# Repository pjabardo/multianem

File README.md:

# multianem - Multiple channel thermistor based CTA anemometer

This projecto has as its objective implement low cost multiple channel thermistor based constant temperature anemometer systems. This projecto includes the KICAD projects for the sensors and data acquisition system.

The main objective is to design a robust, cheap and easily sourced system. By easily sourced system, I mean that the components should be readily available in Brazil.

The project has different parts:

 * `multiname`: Basic board with 8 sensors.
 * `esp32-daq-board`: Data acquisition system for 32 channels
 * `multianem-box`: 3D printed/CNC casing for the system.
 * `multianemdaq`: embedded data acquisition software for the ESP32
 * Other software: data acquisition for Julia, R and Python (nothing to see yet...)

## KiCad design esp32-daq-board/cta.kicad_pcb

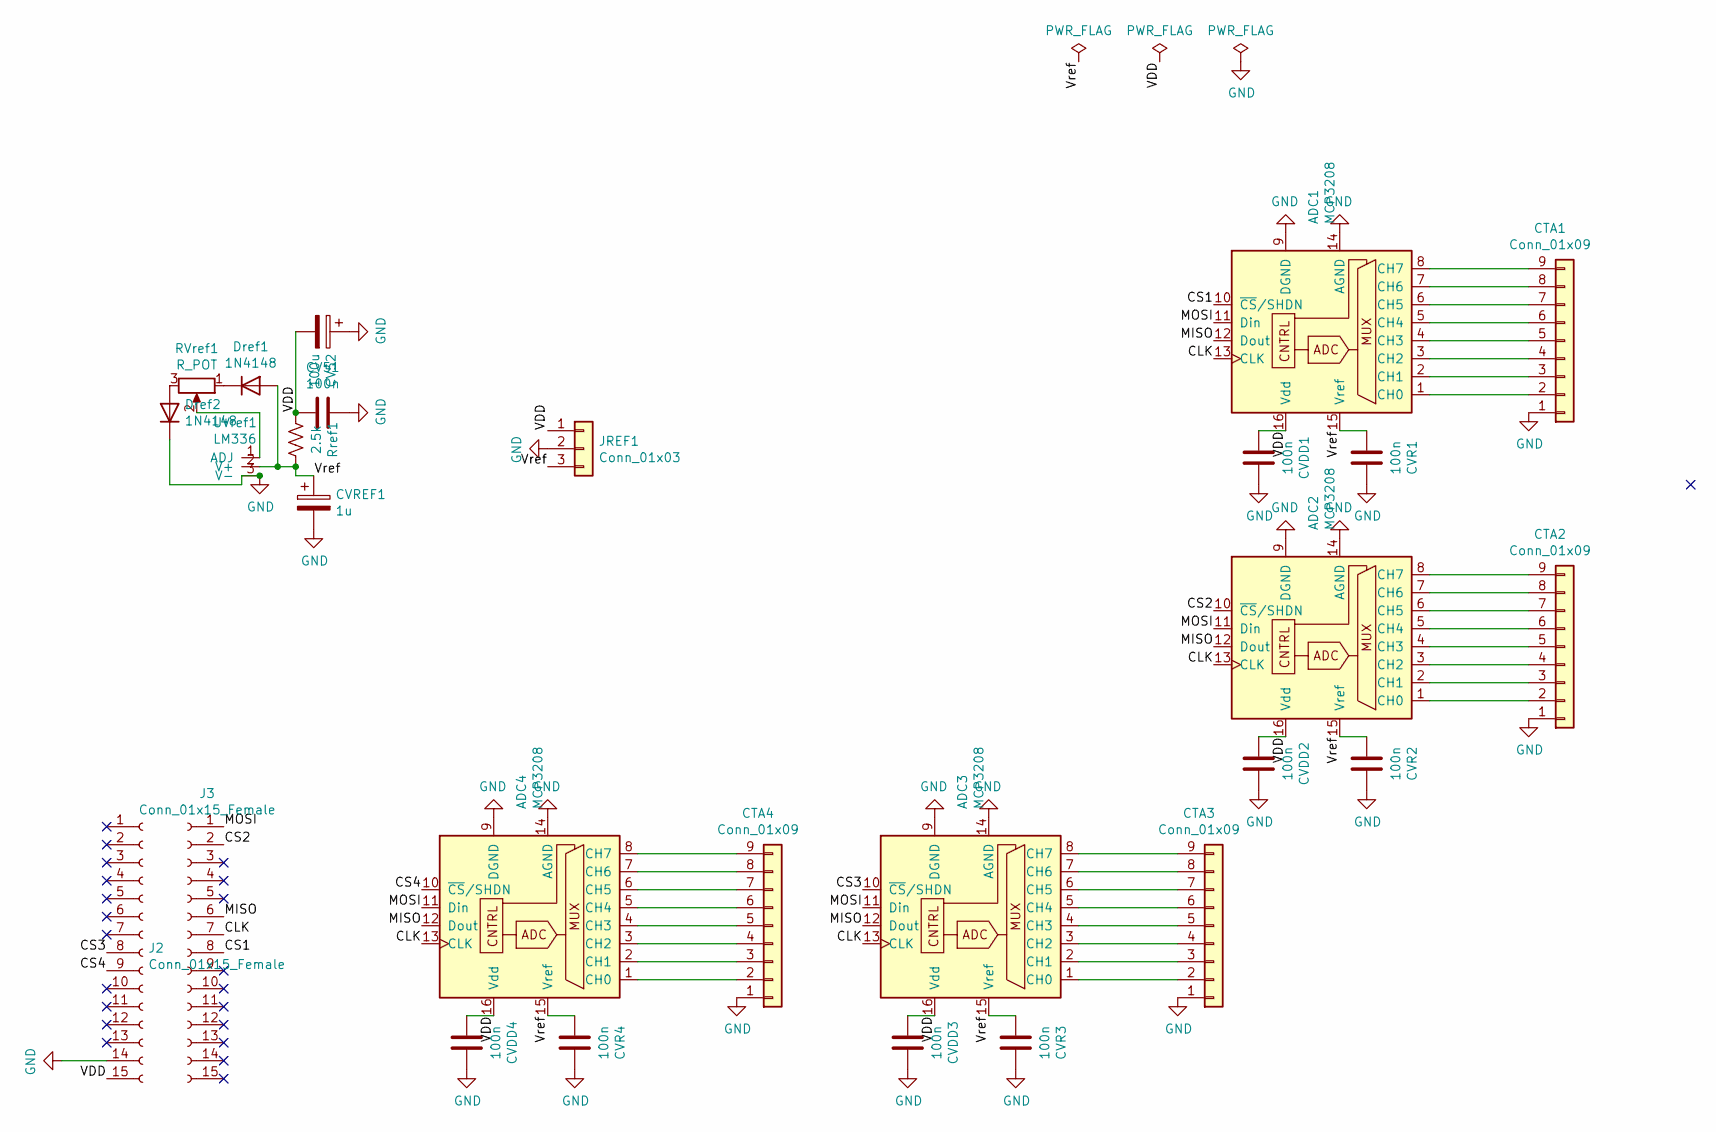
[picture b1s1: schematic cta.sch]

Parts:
ADC1, ADC2, ADC3, ADC4: MCP3208; DIP-16_W7.62mm_LongPads
CTA1, CTA2, CTA3, CTA4: Conn_01x09; PinHeader_1x09_P2.54mm_Vertical
CV51: 100n; C_Rect_L7.2mm_W3.0mm_P5.00mm_FKS2_FKP2_MKS2_MKP2
CV52: 100u; CP_Radial_D6.3mm_P2.50mm
CVDD1, CVDD2, CVDD3, CVDD4: 100n; C_Rect_L7.2mm_W3.0mm_P5.00mm_FKS2_FKP2_MKS2_MKP2
CVR1, CVR2, CVR3, CVR4: 100n; C_Rect_L7.2mm_W3.0mm_P5.00mm_FKS2_FKP2_MKS2_MKP2
CVREF1: 1u; CP_Radial_D4.0mm_P2.00mm
Dref1, Dref2: 1N4148; D_DO-35_SOD27_P7.62mm_Horizontal
J2, J3: Conn_01x15_Female; PinSocket_1x15_P2.54mm_Vertical
JREF1: Conn_01x03; TerminalBlock_bornier-3_P5.08mm
RVref1: R_POT; Potentiometer_Bourns_3296W_Vertical
Rref1: 2.5k; R_Axial_DIN0207_L6.3mm_D2.5mm_P10.16mm_Horizontal
UVref1: LM336; TO-92L_Inline_Wide

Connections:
/CLK: ADC1.13 (CLK), ADC2.13 (CLK), ADC3.13 (CLK), ADC4.13 (CLK), J3.7
/CS1: ADC1.10 (~CS~/SHDN), J3.8
/CS2: ADC2.10 (~CS~/SHDN), J3.2
/CS3: ADC3.10 (~CS~/SHDN), J2.8
/CS4: ADC4.10 (~CS~/SHDN), J2.9
/MISO: ADC1.12 (Dout), ADC2.12 (Dout), ADC3.12 (Dout), ADC4.12 (Dout), J3.6
/MOSI: ADC1.11 (Din), ADC2.11 (Din), ADC3.11 (Din), ADC4.11 (Din), J3.1
/VDD: ADC1.16 (Vdd), ADC2.16 (Vdd), ADC3.16 (Vdd), ADC4.16 (Vdd), CV51.2, CV52.2, CVDD1.2, CVDD2.2, CVDD3.2, CVDD4.2, J2.15, JREF1.1, Rref1.2
/Vref: ADC1.15 (Vref), ADC2.15 (Vref), ADC3.15 (Vref), ADC4.15 (Vref), CVR1.2, CVR2.2, CVR3.2, CVR4.2, CVREF1.1, Dref1.2 (A), JREF1.3, Rref1.1, UVref1.2 (V+)
GND: ADC1.9 (DGND), ADC1.14 (AGND), ADC2.9 (DGND), ADC2.14 (AGND), ADC3.9 (DGND), ADC3.14 (AGND), ADC4.9 (DGND), ADC4.14 (AGND), CTA1.1, CTA2.1, CTA3.1, CTA4.1, CV51.1, CV52.1, CVDD1.1, CVDD2.1, CVDD3.1, CVDD4.1, CVR1.1, CVR2.1, CVR3.1, CVR4.1, CVREF1.2, Dref2.1 (K), J2.14, JREF1.2, UVref1.3 (V-)
unnamed: ADC1.1 (CH0), CTA1.2
unnamed: ADC1.2 (CH1), CTA1.3
unnamed: ADC1.3 (CH2), CTA1.4
unnamed: ADC1.4 (CH3), CTA1.5
unnamed: ADC1.5 (CH4), CTA1.6
unnamed: ADC1.6 (CH5), CTA1.7
unnamed: ADC1.7 (CH6), CTA1.8
unnamed: ADC1.8 (CH7), CTA1.9
unnamed: ADC2.1 (CH0), CTA2.2
unnamed: ADC2.2 (CH1), CTA2.3
unnamed: ADC2.3 (CH2), CTA2.4
unnamed: ADC2.4 (CH3), CTA2.5
unnamed: ADC2.5 (CH4), CTA2.6
unnamed: ADC2.6 (CH5), CTA2.7
unnamed: ADC2.7 (CH6), CTA2.8
unnamed: ADC2.8 (CH7), CTA2.9
unnamed: ADC3.1 (CH0), CTA3.2
unnamed: ADC3.2 (CH1), CTA3.3
unnamed: ADC3.3 (CH2), CTA3.4
unnamed: ADC3.4 (CH3), CTA3.5
unnamed: ADC3.5 (CH4), CTA3.6
unnamed: ADC3.6 (CH5), CTA3.7
unnamed: ADC3.7 (CH6), CTA3.8
unnamed: ADC3.8 (CH7), CTA3.9
unnamed: ADC4.1 (CH0), CTA4.2
unnamed: ADC4.2 (CH1), CTA4.3
unnamed: ADC4.3 (CH2), CTA4.4
unnamed: ADC4.4 (CH3), CTA4.5
unnamed: ADC4.5 (CH4), CTA4.6
unnamed: ADC4.6 (CH5), CTA4.7
unnamed: ADC4.7 (CH6), CTA4.8
unnamed: ADC4.8 (CH7), CTA4.9
unnamed: Dref1.1 (K), RVref1.1
unnamed: Dref2.2 (A), RVref1.3
unnamed: RVref1.2, UVref1.1 (ADJ)

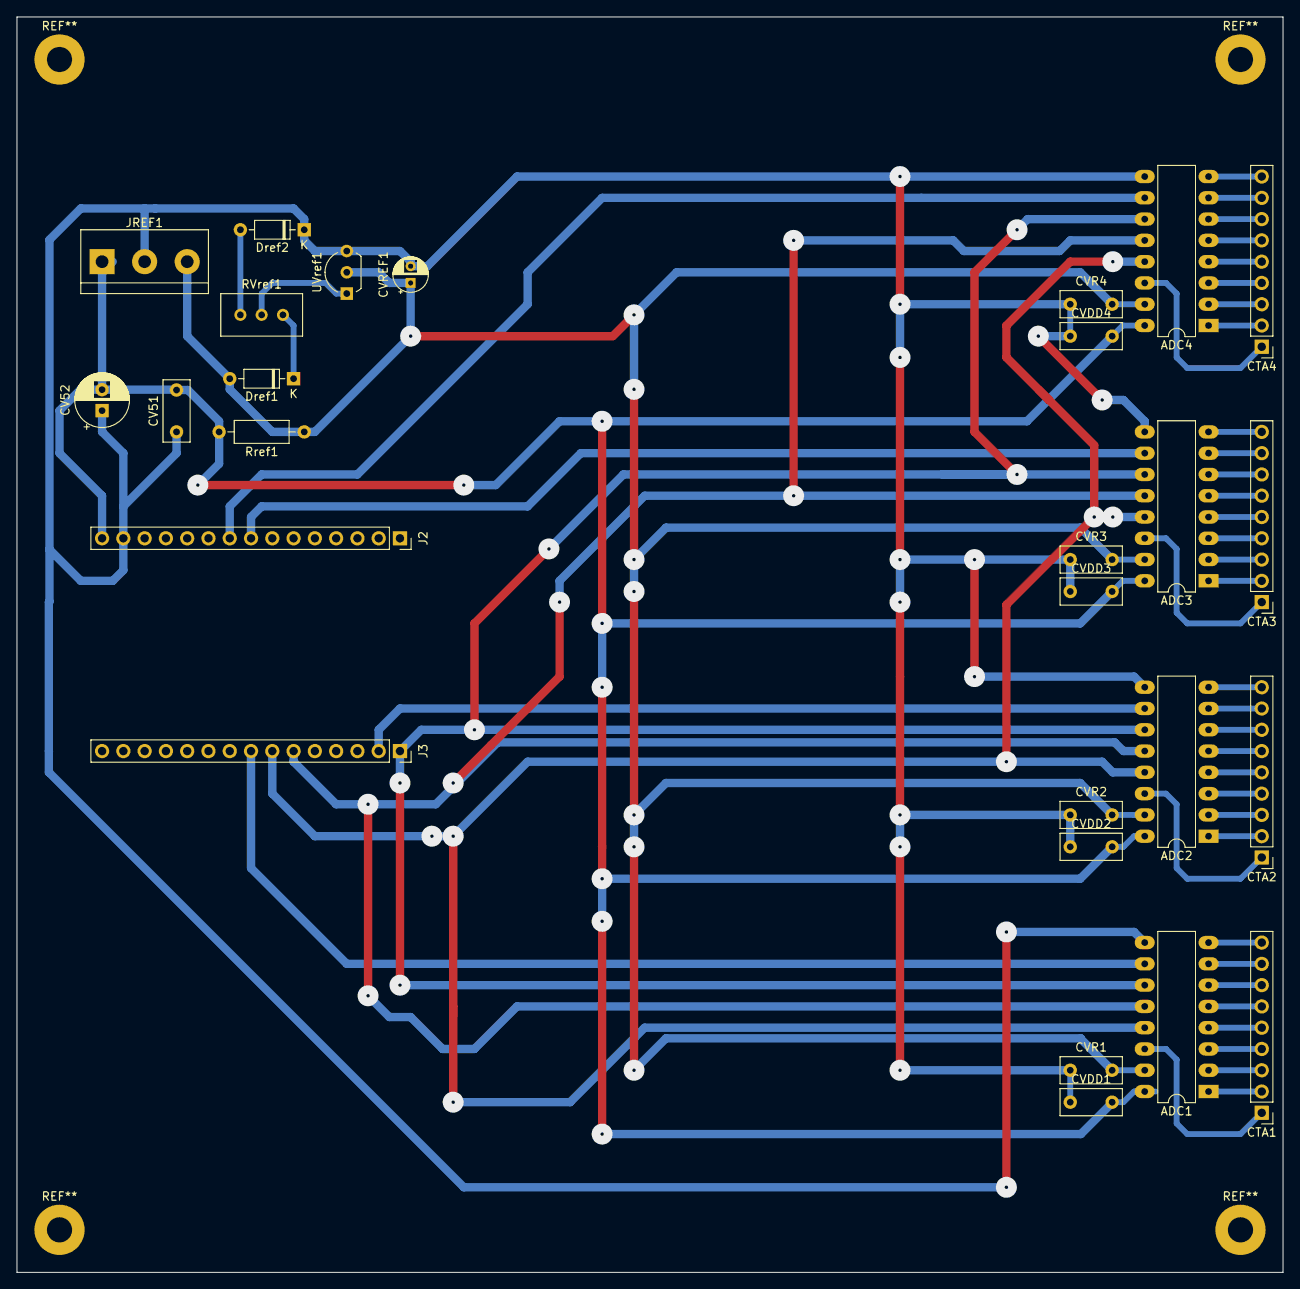
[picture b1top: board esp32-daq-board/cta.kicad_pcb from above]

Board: 2 copper layers, 151.1 x 149.9 mm, 27 parts (0 on the bottom side), 45 nets.

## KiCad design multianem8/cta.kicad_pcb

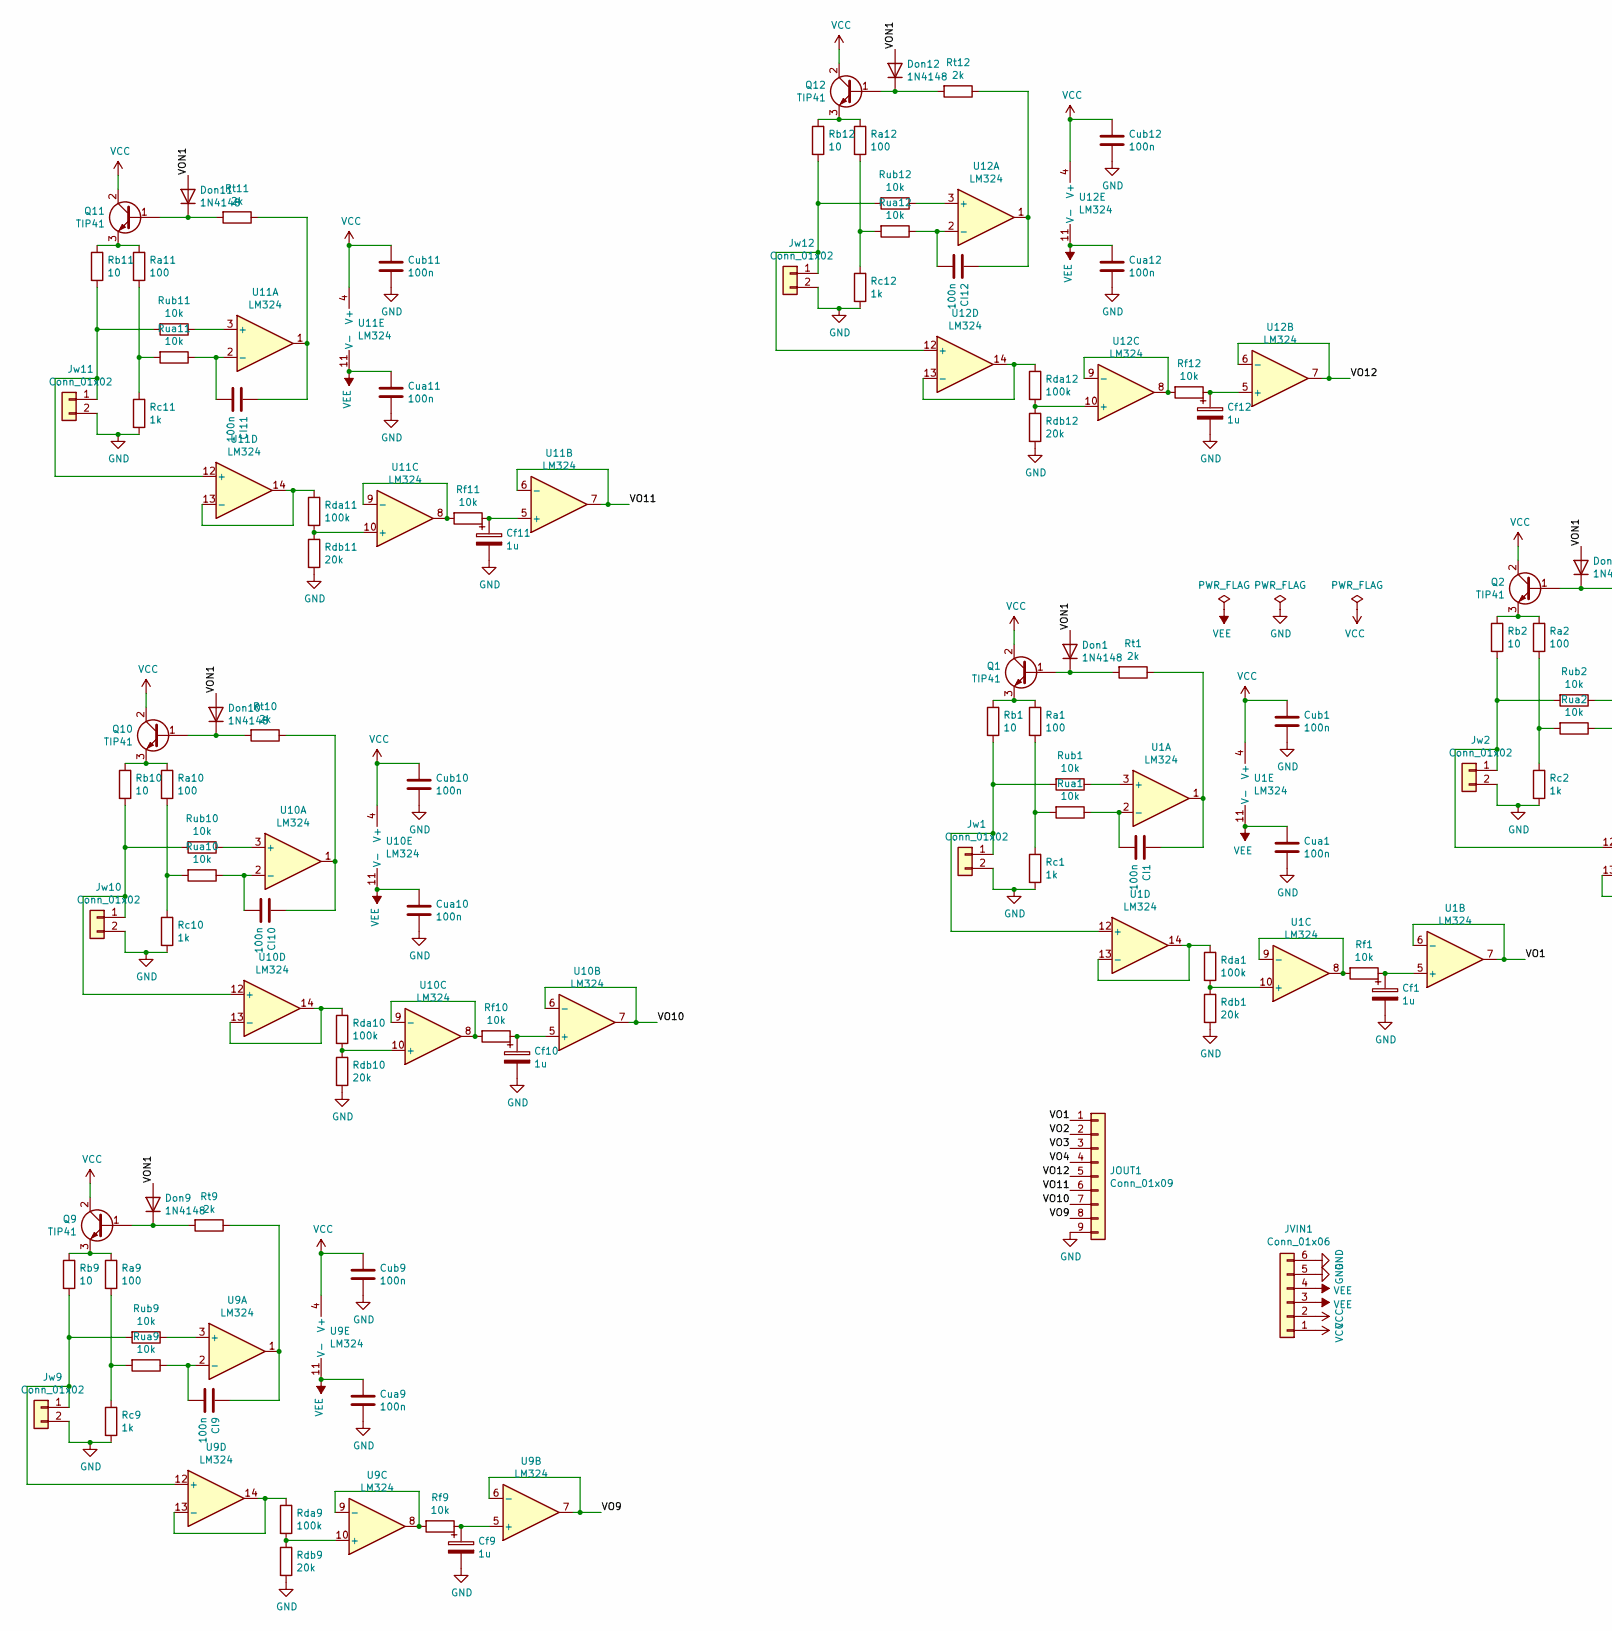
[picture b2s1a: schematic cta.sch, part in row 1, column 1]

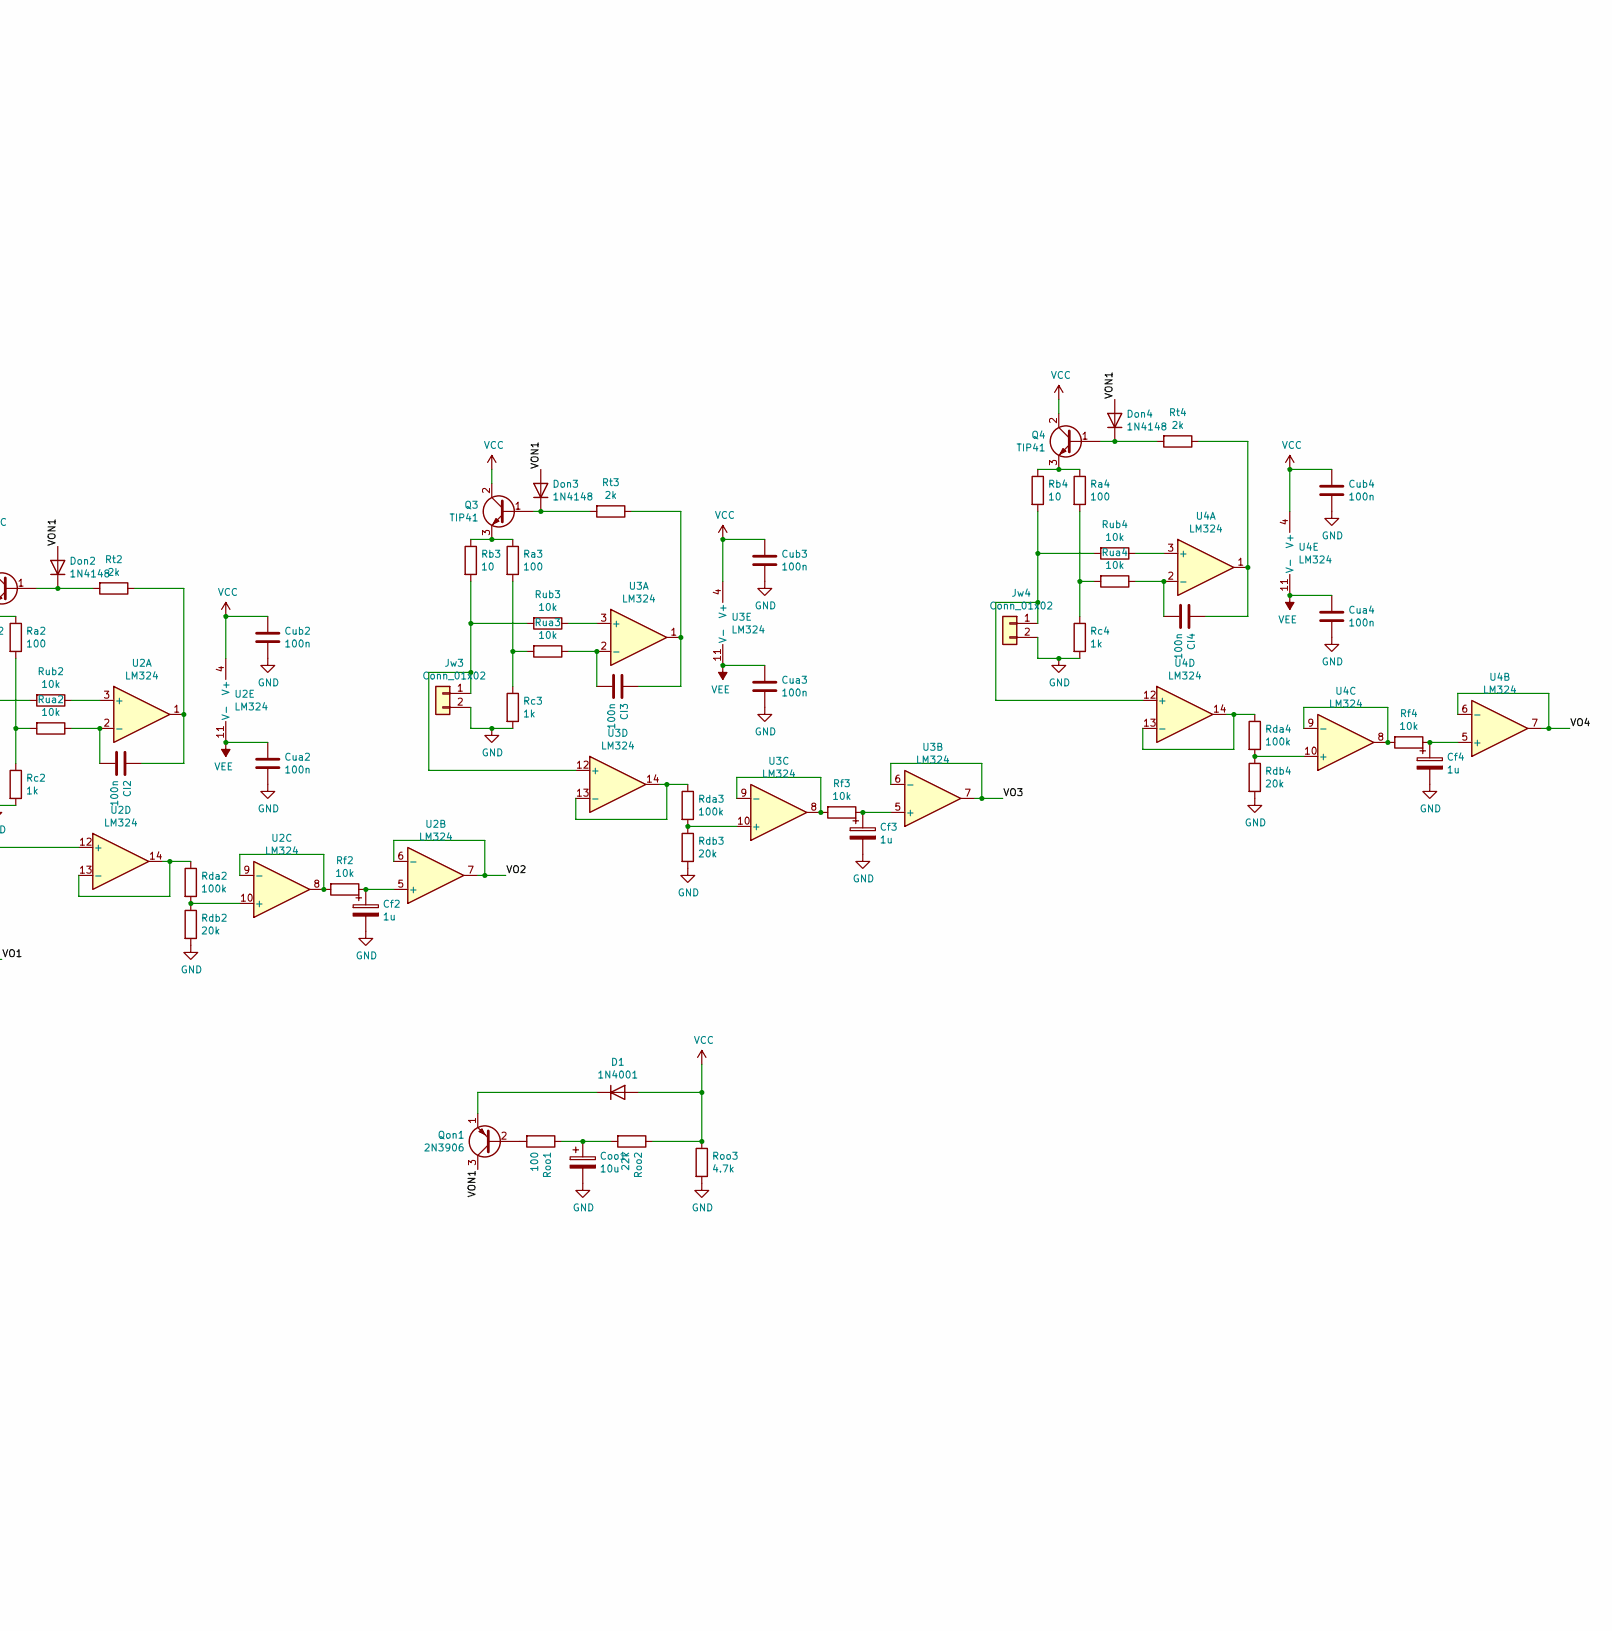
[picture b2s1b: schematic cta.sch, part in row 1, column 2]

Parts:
CI1, CI2, CI3, CI4, CI9, CI10, CI11, CI12: 100n; C_Rect_L7.2mm_W3.5mm_P5.00mm_FKS2_FKP2_MKS2_MKP2
Cf1, Cf2, Cf3, Cf4, Cf9, Cf10, Cf11, Cf12: 1u; CP_Radial_D5.0mm_P2.50mm
Coo1: 10u; CP_Radial_D5.0mm_P2.50mm
Cua1, Cua2, Cua3, Cua4, Cua9, Cua10, Cua11, Cua12: 100n; C_Disc_D5.0mm_W2.5mm_P2.50mm
Cub1, Cub2, Cub3, Cub4, Cub9, Cub10, Cub11, Cub12: 100n; C_Disc_D5.0mm_W2.5mm_P2.50mm
D1: 1N4001; D_DO-41_SOD81_P10.16mm_Horizontal
Don1, Don2, Don3, Don4, Don9, Don10, Don11, Don12: 1N4148; D_DO-35_SOD27_P7.62mm_Horizontal
JOUT1: Conn_01x09; PinHeader_1x09_P2.54mm_Vertical
JVIN1: Conn_01x06; TerminalBlock_bornier-6_P5.08mm
Jw1, Jw2, Jw3, Jw4, Jw9, Jw10, Jw11, Jw12: Conn_01x02; PinHeader_1x02_P2.54mm_Vertical
Q1, Q2, Q3, Q4, Q9, Q10, Q11, Q12: TIP41; TO-220-3_Vertical
Qon1: 2N3906; TO-92_Inline_Wide
Ra1, Ra2, Ra3, Ra4, Ra9, Ra10, Ra11, Ra12: 100; R_Axial_DIN0207_L6.3mm_D2.5mm_P10.16mm_Horizontal
Rb1, Rb2, Rb3, Rb4, Rb9, Rb10, Rb11, Rb12: 10; R_Axial_DIN0414_L11.9mm_D4.5mm_P15.24mm_Horizontal
Rc1, Rc2, Rc3, Rc4, Rc9, Rc10, Rc11, Rc12: 1k; R_Axial_DIN0207_L6.3mm_D2.5mm_P10.16mm_Horizontal
Rda1, Rda2, Rda3, Rda4, Rda9, Rda10, Rda11, Rda12: 100k; R_Axial_DIN0207_L6.3mm_D2.5mm_P10.16mm_Horizontal
Rdb1, Rdb2, Rdb3, Rdb4, Rdb9, Rdb10, Rdb11, Rdb12: 20k; R_Axial_DIN0207_L6.3mm_D2.5mm_P10.16mm_Horizontal
Rf1, Rf2, Rf3, Rf4, Rf9, Rf10, Rf11, Rf12: 10k; R_Axial_DIN0207_L6.3mm_D2.5mm_P10.16mm_Horizontal
Roo1: 100; R_Axial_DIN0207_L6.3mm_D2.5mm_P10.16mm_Horizontal
Roo2: 22k; R_Axial_DIN0207_L6.3mm_D2.5mm_P10.16mm_Horizontal
Roo3: 4.7k; R_Axial_DIN0207_L6.3mm_D2.5mm_P10.16mm_Horizontal
Rt1, Rt2, Rt3, Rt4, Rt9, Rt10, Rt11, Rt12: 2k; R_Axial_DIN0207_L6.3mm_D2.5mm_P10.16mm_Horizontal
Rua1, Rua2, Rua3, Rua4, Rua9, Rua10, Rua11, Rua12: 10k; R_Axial_DIN0207_L6.3mm_D2.5mm_P10.16mm_Horizontal
Rub1, Rub2, Rub3, Rub4, Rub9, Rub10, Rub11, Rub12: 10k; R_Axial_DIN0207_L6.3mm_D2.5mm_P10.16mm_Horizontal
U1, U2, U3, U4, U9, U10, U11, U12: LM324; DIP-14_W7.62mm_LongPads

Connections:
/VO1: JOUT1.1, U1.6 (-), U1.7
/VO2: JOUT1.2, U2.6 (-), U2.7
/VO3: JOUT1.3, U3.6 (-), U3.7
/VO4: JOUT1.4, U4.6 (-), U4.7
/VO9: JOUT1.8, U9.6 (-), U9.7
/VO10: JOUT1.7, U10.6 (-), U10.7
/VO11: JOUT1.6, U11.6 (-), U11.7
/VO12: JOUT1.5, U12.6 (-), U12.7
/VON1: Don1.2 (A), Don2.2 (A), Don3.2 (A), Don4.2 (A), Don9.2 (A), Don10.2 (A), Don11.2 (A), Don12.2 (A), Qon1.3 (C)
GND: Cf1.2, Cf2.2, Cf3.2, Cf4.2, Cf9.2, Cf10.2, Cf11.2, Cf12.2, Coo1.2, Cua1.2, Cua2.2, Cua3.2, Cua4.2, Cua9.2, Cua10.2, Cua11.2, Cua12.2, Cub1.2, Cub2.2, Cub3.2, Cub4.2, Cub9.2, Cub10.2, Cub11.2, Cub12.2, JOUT1.9, JVIN1.5, JVIN1.6, Jw1.2, Jw2.2, Jw3.2, Jw4.2, Jw9.2, Jw10.2, Jw11.2, Jw12.2, Rc1.2, Rc2.2, Rc3.2, Rc4.2, Rc9.2, Rc10.2, Rc11.2, Rc12.2, Rdb1.2, Rdb2.2, Rdb3.2, Rdb4.2, Rdb9.2, Rdb10.2, Rdb11.2, Rdb12.2, Roo3.2
unnamed: CI1.1, Rt1.1, U1.1
unnamed: CI1.2, Rua1.1, U1.2 (-)
unnamed: CI2.1, Rt2.1, U2.1
unnamed: CI2.2, Rua2.1, U2.2 (-)
unnamed: CI3.1, Rt3.1, U3.1
unnamed: CI3.2, Rua3.1, U3.2 (-)
unnamed: CI4.1, Rt4.1, U4.1
unnamed: CI4.2, Rua4.1, U4.2 (-)
unnamed: CI9.1, Rt9.1, U9.1
unnamed: CI9.2, Rua9.1, U9.2 (-)
unnamed: CI10.1, Rt10.1, U10.1
unnamed: CI10.2, Rua10.1, U10.2 (-)
unnamed: CI11.1, Rt11.1, U11.1
unnamed: CI11.2, Rua11.1, U11.2 (-)
unnamed: CI12.1, Rt12.1, U12.1
unnamed: CI12.2, Rua12.1, U12.2 (-)
unnamed: Cf1.1, Rf1.1, U1.5 (+)
unnamed: Cf2.1, Rf2.1, U2.5 (+)
unnamed: Cf3.1, Rf3.1, U3.5 (+)
unnamed: Cf4.1, Rf4.1, U4.5 (+)
unnamed: Cf9.1, Rf9.1, U9.5 (+)
unnamed: Cf10.1, Rf10.1, U10.5 (+)
unnamed: Cf11.1, Rf11.1, U11.5 (+)
unnamed: Cf12.1, Rf12.1, U12.5 (+)
unnamed: Coo1.1, Roo1.1, Roo2.2
unnamed: D1.1 (K), Qon1.1 (E)
unnamed: Don1.1 (K), Q1.1 (B), Rt1.2
unnamed: Don2.1 (K), Q2.1 (B), Rt2.2
unnamed: Don3.1 (K), Q3.1 (B), Rt3.2
unnamed: Don4.1 (K), Q4.1 (B), Rt4.2
unnamed: Don9.1 (K), Q9.1 (B), Rt9.2
unnamed: Don10.1 (K), Q10.1 (B), Rt10.2
unnamed: Don11.1 (K), Q11.1 (B), Rt11.2
unnamed: Don12.1 (K), Q12.1 (B), Rt12.2
unnamed: Jw1.1, Rb1.2, Rub1.2, U1.12 (+)
unnamed: Jw2.1, Rb2.2, Rub2.2, U2.12 (+)
unnamed: Jw3.1, Rb3.2, Rub3.2, U3.12 (+)
unnamed: Jw4.1, Rb4.2, Rub4.2, U4.12 (+)
unnamed: Jw9.1, Rb9.2, Rub9.2, U9.12 (+)
unnamed: Jw10.1, Rb10.2, Rub10.2, U10.12 (+)
unnamed: Jw11.1, Rb11.2, Rub11.2, U11.12 (+)
unnamed: Jw12.1, Rb12.2, Rub12.2, U12.12 (+)
unnamed: Q1.3 (E), Ra1.1, Rb1.1
unnamed: Q2.3 (E), Ra2.1, Rb2.1
unnamed: Q3.3 (E), Ra3.1, Rb3.1
unnamed: Q4.3 (E), Ra4.1, Rb4.1
unnamed: Q9.3 (E), Ra9.1, Rb9.1
unnamed: Q10.3 (E), Ra10.1, Rb10.1
unnamed: Q11.3 (E), Ra11.1, Rb11.1
unnamed: Q12.3 (E), Ra12.1, Rb12.1
unnamed: Qon1.2 (B), Roo1.2
unnamed: Ra1.2, Rc1.1, Rua1.2
unnamed: Ra2.2, Rc2.1, Rua2.2
unnamed: Ra3.2, Rc3.1, Rua3.2
unnamed: Ra4.2, Rc4.1, Rua4.2
unnamed: Ra9.2, Rc9.1, Rua9.2
unnamed: Ra10.2, Rc10.1, Rua10.2
unnamed: Ra11.2, Rc11.1, Rua11.2
unnamed: Ra12.2, Rc12.1, Rua12.2
unnamed: Rda1.1, U1.13 (-), U1.14
unnamed: Rda1.2, Rdb1.1, U1.10 (+)
unnamed: Rda2.1, U2.13 (-), U2.14
unnamed: Rda2.2, Rdb2.1, U2.10 (+)
unnamed: Rda3.1, U3.13 (-), U3.14
unnamed: Rda3.2, Rdb3.1, U3.10 (+)
unnamed: Rda4.1, U4.13 (-), U4.14
unnamed: Rda4.2, Rdb4.1, U4.10 (+)
unnamed: Rda9.1, U9.13 (-), U9.14
unnamed: Rda9.2, Rdb9.1, U9.10 (+)
unnamed: Rda10.1, U10.13 (-), U10.14
unnamed: Rda10.2, Rdb10.1, U10.10 (+)
unnamed: Rda11.1, U11.13 (-), U11.14
unnamed: Rda11.2, Rdb11.1, U11.10 (+)
unnamed: Rda12.1, U12.13 (-), U12.14
unnamed: Rda12.2, Rdb12.1, U12.10 (+)
unnamed: Rf1.2, U1.8, U1.9 (-)
unnamed: Rf2.2, U2.8, U2.9 (-)
unnamed: Rf3.2, U3.8, U3.9 (-)
unnamed: Rf4.2, U4.8, U4.9 (-)
unnamed: Rf9.2, U9.8, U9.9 (-)
unnamed: Rf10.2, U10.8, U10.9 (-)
unnamed: Rf11.2, U11.8, U11.9 (-)
unnamed: Rf12.2, U12.8, U12.9 (-)
unnamed: Rub1.1, U1.3 (+)
unnamed: Rub2.1, U2.3 (+)
unnamed: Rub3.1, U3.3 (+)
unnamed: Rub4.1, U4.3 (+)
unnamed: Rub9.1, U9.3 (+)
unnamed: Rub10.1, U10.3 (+)
unnamed: Rub11.1, U11.3 (+)
unnamed: Rub12.1, U12.3 (+)
VCC: Cub1.1, Cub2.1, Cub3.1, Cub4.1, Cub9.1, Cub10.1, Cub11.1, Cub12.1, D1.2 (A), JVIN1.1, JVIN1.2, Q1.2 (C), Q2.2 (C), Q3.2 (C), Q4.2 (C), Q9.2 (C), Q10.2 (C), Q11.2 (C), Q12.2 (C), Roo2.1, Roo3.1, U1.4 (V+), U2.4 (V+), U3.4 (V+), U4.4 (V+), U9.4 (V+), U10.4 (V+), U11.4 (V+), U12.4 (V+)
VEE: Cua1.1, Cua2.1, Cua3.1, Cua4.1, Cua9.1, Cua10.1, Cua11.1, Cua12.1, JVIN1.3, JVIN1.4, U1.11 (V-), U2.11 (V-), U3.11 (V-), U4.11 (V-), U9.11 (V-), U10.11 (V-), U11.11 (V-), U12.11 (V-)

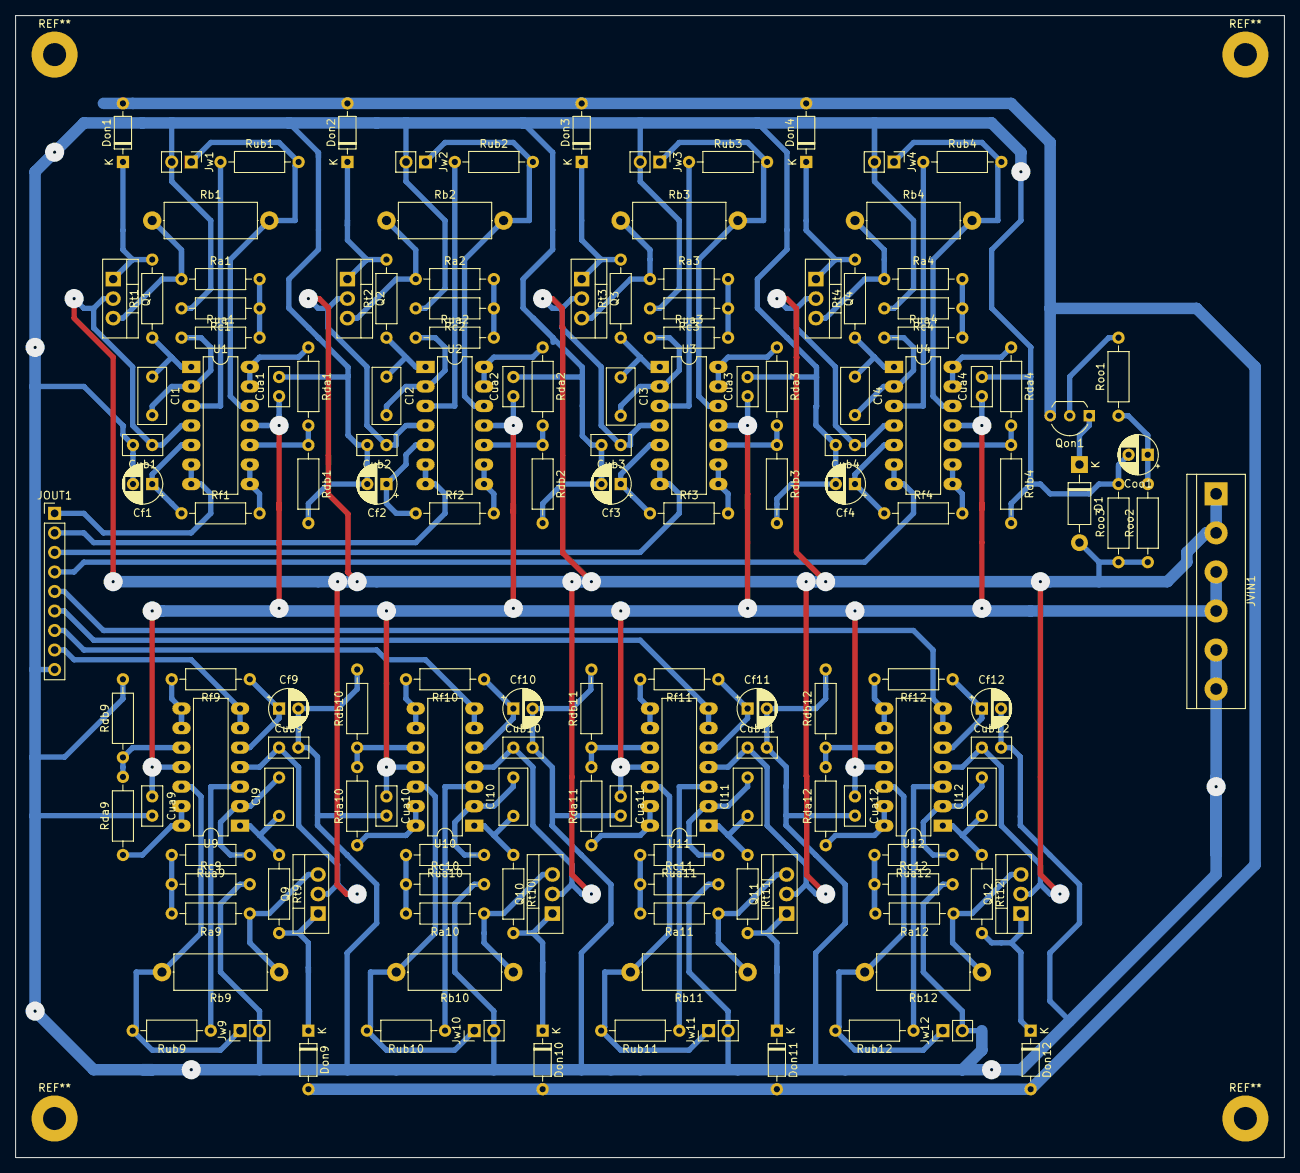
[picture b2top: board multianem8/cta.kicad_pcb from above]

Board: 2 copper layers, 165.1 x 148.6 mm, 144 parts (0 on the bottom side), 103 nets.
